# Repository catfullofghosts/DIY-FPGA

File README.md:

# diy_fpga
A discrete component FPGA designed from scratch

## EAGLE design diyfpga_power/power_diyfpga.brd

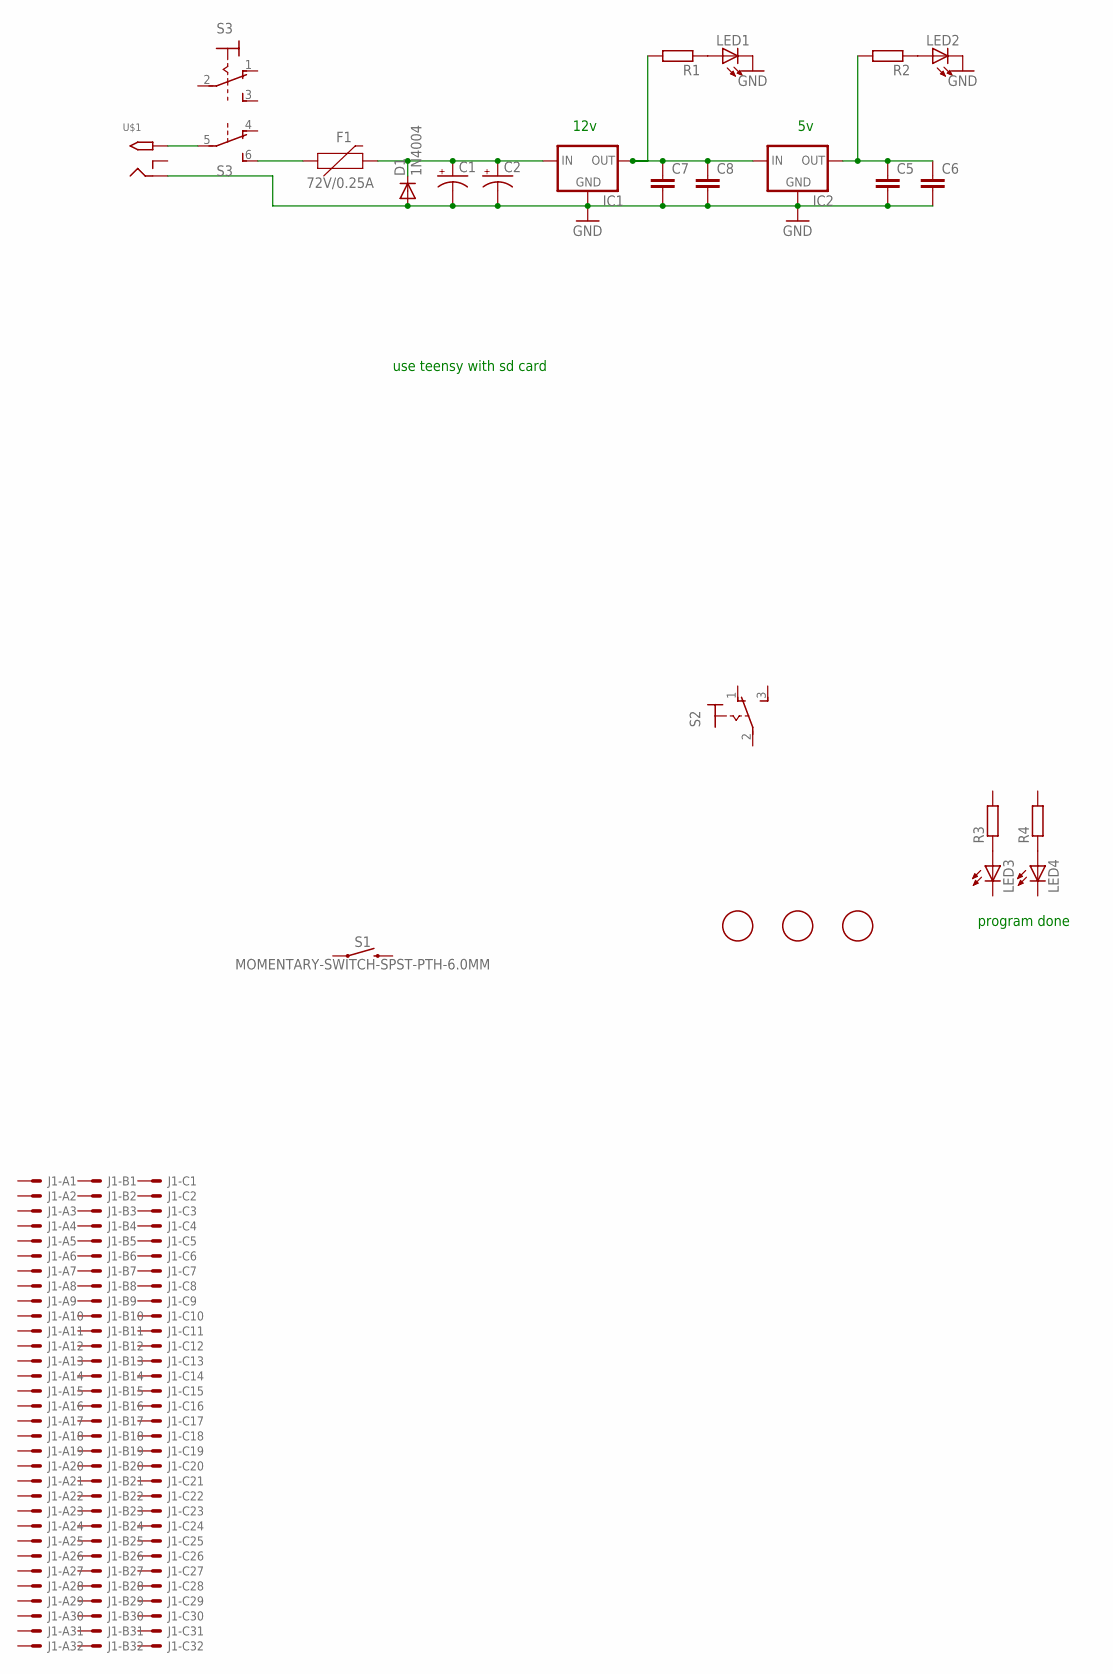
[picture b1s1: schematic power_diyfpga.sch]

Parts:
C1, C2: CPOL-US140CLH-1014; 140CLH-1014
C5, C6, C7, C8: C-EUC0805K; C0805K
D1: 1N4004; DO41-10
F1: 72V/0.25A; PTH
IC1, IC2: 78MXXS
J1: VG96SP; VG96P
LED1, LED2, LED3, LED4: LED3MM
R1, R2, R3, R4: R-EU_R0805; R0805
S1: MOMENTARY-SWITCH-SPST-PTH-6.0MM; TACTILE_SWITCH_PTH_6.0MM
S2: 320-916
S3: 320-938
U$1: 2.1MMJACKTHM; PJ-102A
U$2, U$3, U$4: FIDUCIAL; FIDUCIAL_1MM

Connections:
GND: C1.-, C2.-, C5.2, C6.2, C7.2, C8.2, D1.A, IC1.GND, IC2.GND, LED1.K (C), LED2.K (C), U$1.RING
unnamed: LED3.A, R3.1
unnamed: LED4.A, R4.1
unnamed: F1.P$1 (1), S3.6 (S)
unnamed: C1.+, C2.+, D1.C, F1.P$2 (2), IC1.IN
unnamed: S3.5, U$1.TIP
unnamed: LED1.A, R1.1
unnamed: LED2.A, R2.1
unnamed: C7.1, C8.1, IC1.OUT, IC2.IN, R1.2
unnamed: C5.1, C6.1, IC2.OUT, R2.2

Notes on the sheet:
program done
12v
use teensy with sd card

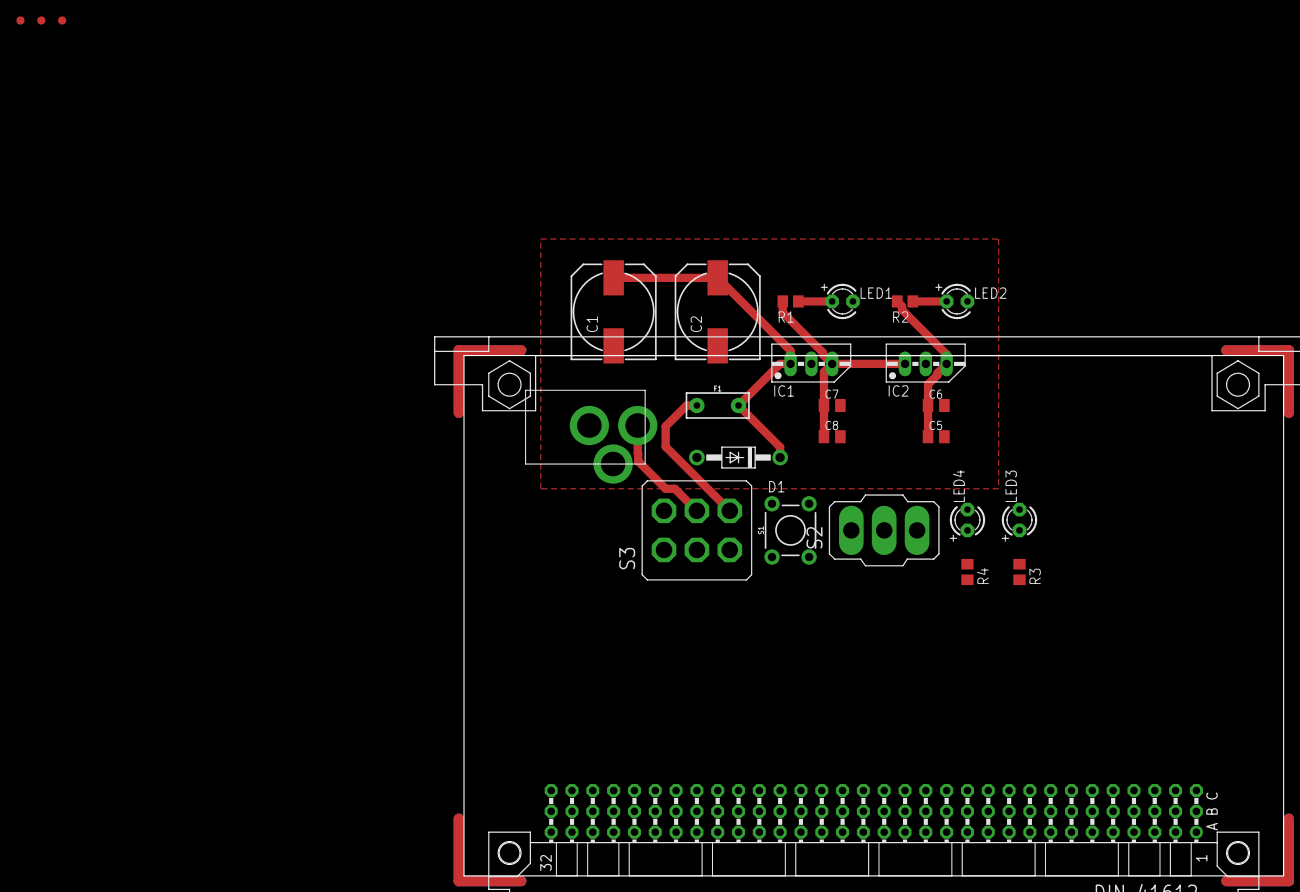
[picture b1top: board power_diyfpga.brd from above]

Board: 2 copper layers, 100.0 x 63.5 mm, 26 parts (0 on the bottom side), 10 nets.

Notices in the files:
parts and their libraries:
SparkFun-Fuses: Licensing: Creative Commons ShareAlike 4.0 International - https://creativecommons.org/licenses/by-sa/4.0
